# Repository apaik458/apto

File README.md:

# Apto

Bimanual manipulation platform
* Two 6-DoF arms + two 1-DoF parallel grippers + 1-DoF neck (total 15 DoF)
* Waveshare servos (CF35-12 + ST3025)
* 3D printed parts + aluminium servo frames

<div align="center">
    
</div>

## Directory Guide

```
apto/
├── API/                           ## API for controlling robot
│   ├── cfservo_sdk/
│   │   ├── __init__.py
│   │   ├── group_sync_read.py
│   │   ├── group_sync_write.py
│   │   └── ...
│   ├── client.py
│   ├── main.py
│   ├── requirements.txt
│   └── README.md
├── Docs/                          ## Information on constructing robot
│   ├── bill_of_materials.md
│   ├── assembly_instructions.md
│   └── README.md
├── Hardware/                      ## Hardware files for 3D printing and PCB
│   ├── PCB/
│   │   ├── robot_pdb.pro
│   │   └── ...
│   ├── STEP/
│   │   ├── base1.step
│   │   └── ...
│   ├── STL/
│   │   ├── base1.stl
│   │   └── ...
│   └── README.md
├── Media/                         ## Images/GIFs
│   ├── robot.jpg
│   └── robot_sim.png
├── LICENSE
└── README.md
```

## Simulation

Refer to the [apto_sim](https://github.com/apaik458/apto_sim) repo for the Maniskill simulation environment

<div align="center">
    
</div>

## Acknowledgements

Inspiration and reference from the following projects:
* [Rakuda-2](https://github.com/ROBOTIS-JAPAN-GIT/rakuda2_example)
* [Hitachi Bimanual Robot](https://monoist.itmedia.co.jp/mn/articles/2603/24/news056.html)
* [SO-ARM100](https://github.com/TheRobotStudio/SO-ARM100)
* LEAP Hand ([API](https://github.com/leap-hand/LEAP_Hand_API), [Power distribution board](https://github.com/leap-hand/LEAP_Power))
* [Techniccontroller Parallel Gripper](https://techniccontroller.com/3d-printed-parallel-gripper/)

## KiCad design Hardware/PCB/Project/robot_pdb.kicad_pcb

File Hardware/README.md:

# Hardware

Files related to physical robot platform

```
Hardware/
├── PCB/    ## PCB files for power distribution board
├── STEP/   ## 3D CAD STEP files
└── STL/    ## 3D CAD STL files
```

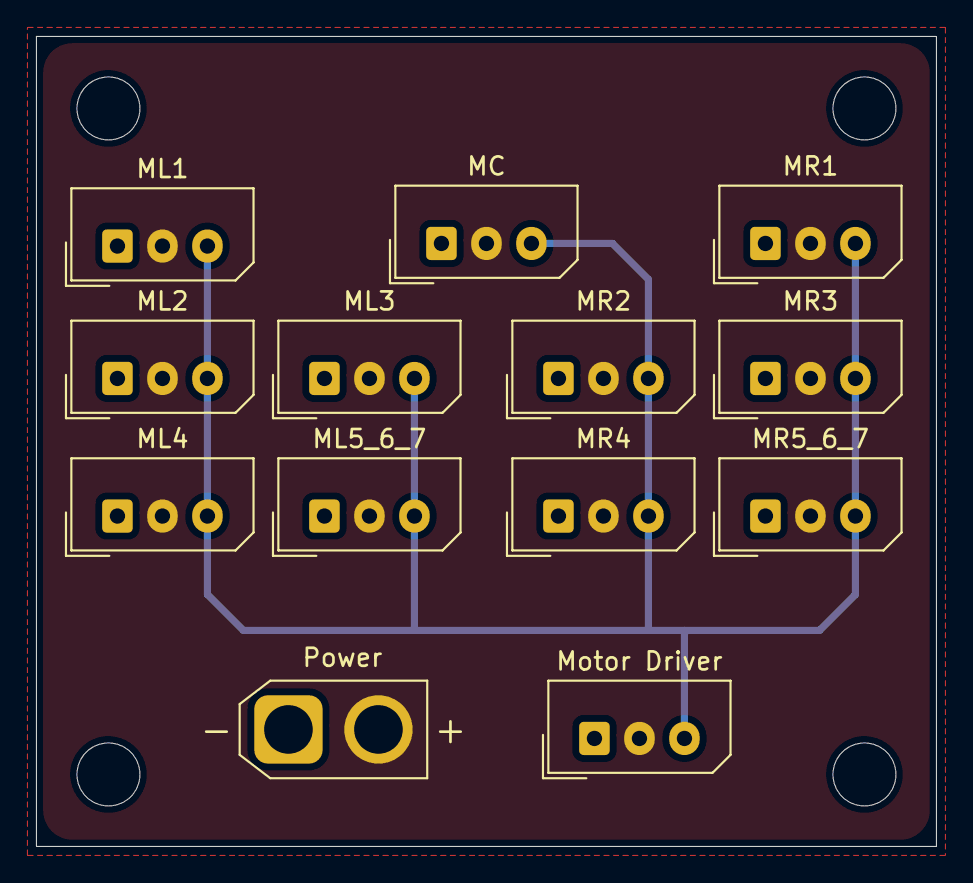
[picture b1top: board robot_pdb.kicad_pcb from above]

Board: 2 copper layers, 50.0 x 45.0 mm, 13 parts (0 on the bottom side), 2 nets.

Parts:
MC: Molex_0022035035; Molex_SPOX_5267-03A_1x03_P2.50mm_Vertical
ML1, ML2, ML3, ML4, ML5_6_7: Molex_0022035035; Molex_SPOX_5267-03A_1x03_P2.50mm_Vertical
MR1, MR2, MR3, MR4, MR5_6_7: Molex_0022035035; Molex_SPOX_5267-03A_1x03_P2.50mm_Vertical
Motor Driver: Molex_0022035035; Molex_SPOX_5267-03A_1x03_P2.50mm_Vertical
Power: AMASS_XT30U-M_1x02_P5.0mm_Vertical

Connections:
GND: MC.1, ML1.1, ML2.1, ML3.1, ML4.1, ML5_6_7.1, MR1.1, MR2.1, MR3.1, MR4.1, MR5_6_7.1, Motor Driver.1, Power.1
VCC: MC.2, ML1.2, ML2.2, ML3.2, ML4.2, ML5_6_7.2, MR1.2, MR2.2, MR3.2, MR4.2, MR5_6_7.2, Motor Driver.2, Power.2
